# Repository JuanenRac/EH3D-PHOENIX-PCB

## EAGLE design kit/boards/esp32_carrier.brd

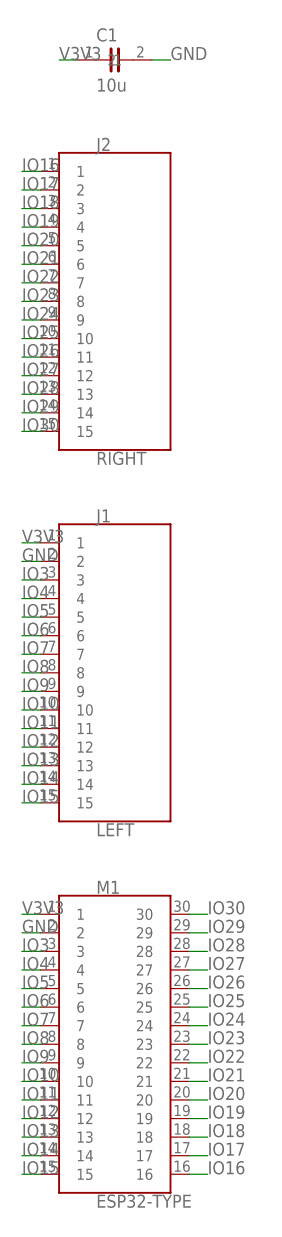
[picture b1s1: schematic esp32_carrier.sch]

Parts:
C1: 10u; CHIP-0805
J1: LEFT; HDR-1X15
J2: RIGHT; HDR-1X15
M1: ESP32-TYPE; MODULE-ESP32-TYPE

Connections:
GND: C1.2, J1.2, M1.2
IO3: J1.3, M1.3
IO4: J1.4, M1.4
IO5: J1.5, M1.5
IO6: J1.6, M1.6
IO7: J1.7, M1.7
IO8: J1.8, M1.8
IO9: J1.9, M1.9
IO10: J1.10, M1.10
IO11: J1.11, M1.11
IO12: J1.12, M1.12
IO13: J1.13, M1.13
IO14: J1.14, M1.14
IO15: J1.15, M1.15
IO16: J2.1, M1.16
IO17: J2.2, M1.17
IO18: J2.3, M1.18
IO19: J2.4, M1.19
IO20: J2.5, M1.20
IO21: J2.6, M1.21
IO22: J2.7, M1.22
IO23: J2.8, M1.23
IO24: J2.9, M1.24
IO25: J2.10, M1.25
IO26: J2.11, M1.26
IO27: J2.12, M1.27
IO28: J2.13, M1.28
IO29: J2.14, M1.29
IO30: J2.15, M1.30
V3V3: C1.1, J1.1, M1.1

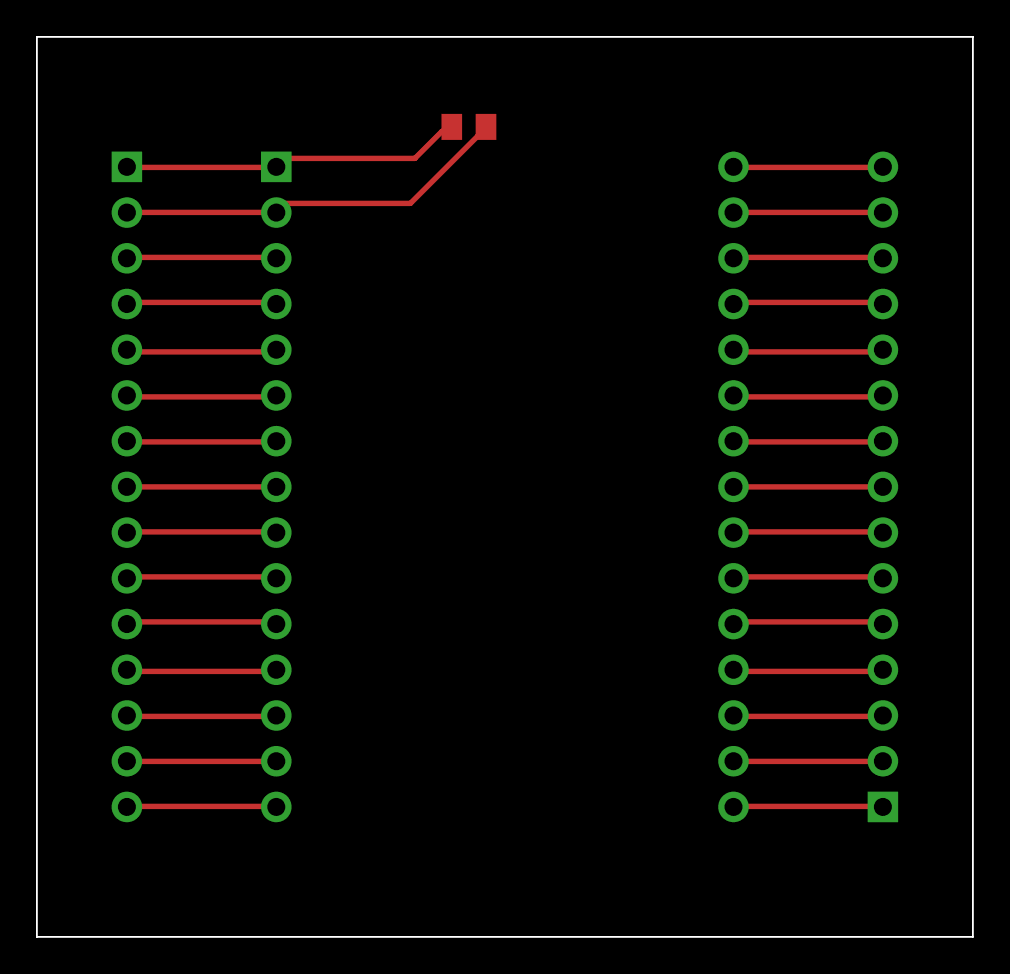
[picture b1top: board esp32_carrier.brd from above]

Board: 1 copper layer, 52.0 x 50.0 mm, 4 parts (0 on the bottom side), 30 nets.

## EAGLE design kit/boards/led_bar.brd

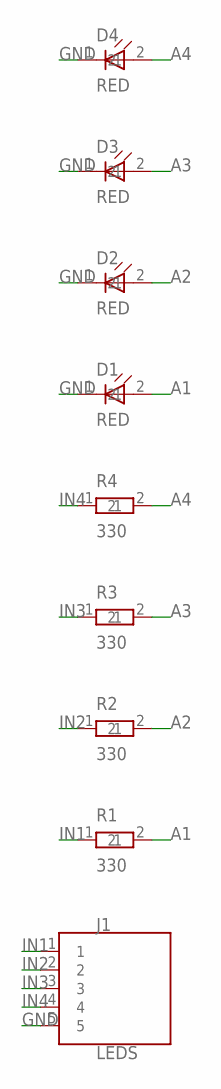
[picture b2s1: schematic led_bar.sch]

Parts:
D1, D2, D3, D4: RED; LED-0603
J1: LEDS; HDR-1X05
R1, R2, R3, R4: 330; CHIP-0603

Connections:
A1: D1.2, R1.2
A2: D2.2, R2.2
A3: D3.2, R3.2
A4: D4.2, R4.2
GND: D1.1, D2.1, D3.1, D4.1, J1.5
IN1: J1.1, R1.1
IN2: J1.2, R2.1
IN3: J1.3, R3.1
IN4: J1.4, R4.1

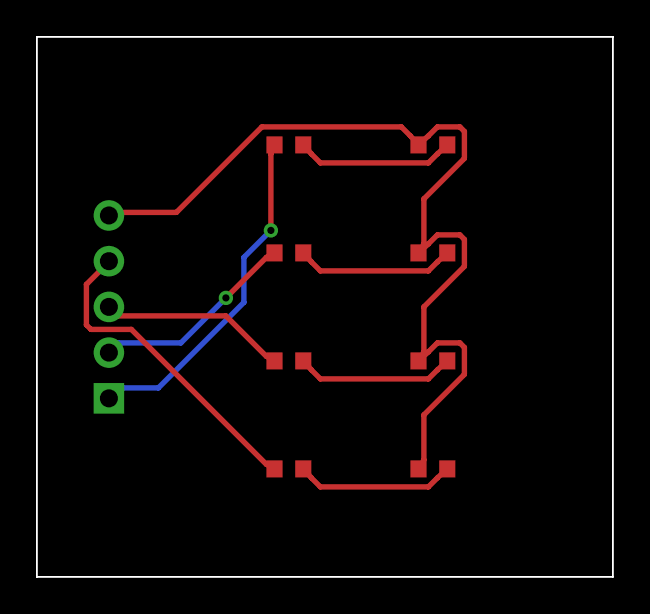
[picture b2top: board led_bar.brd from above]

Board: 2 copper layers, 32.0 x 30.0 mm, 9 parts (0 on the bottom side), 9 nets.

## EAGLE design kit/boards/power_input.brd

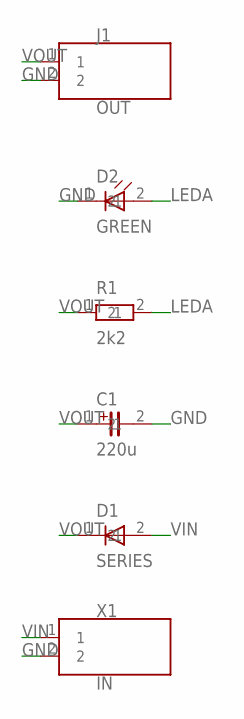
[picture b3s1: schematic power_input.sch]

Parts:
C1: 220u; C-ELEC-D8
D1: SERIES; SOD-123
D2: GREEN; LED-0805
J1: OUT; HDR-1X02
R1: 2k2; CHIP-1206
X1: IN; TERM-2P-5.0

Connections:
GND: C1.2, D2.1, J1.2, X1.2
LEDA: D2.2, R1.2
VIN: D1.2, X1.1
VOUT: C1.1, D1.1, J1.1, R1.1

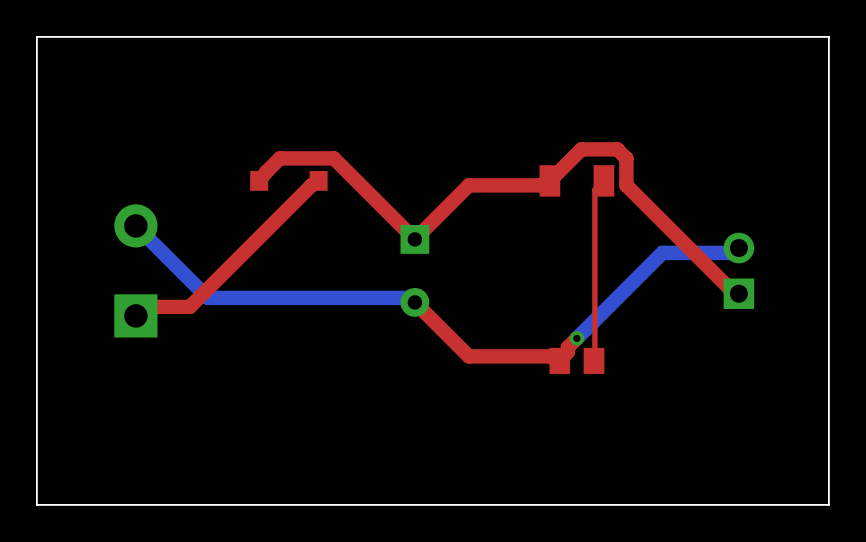
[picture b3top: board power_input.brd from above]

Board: 2 copper layers, 44.0 x 26.0 mm, 6 parts (0 on the bottom side), 4 nets.

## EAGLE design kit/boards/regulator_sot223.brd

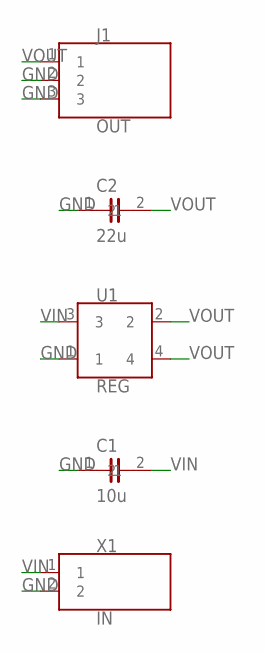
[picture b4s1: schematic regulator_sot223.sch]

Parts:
C1: 10u; CHIP-0805
C2: 22u; CHIP-0805
J1: OUT; HDR-1X03
U1: REG; SOT-223
X1: IN; TERM-2P-5.0

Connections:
GND: C1.1, C2.1, J1.2, J1.3, U1.1, X1.2
VIN: C1.2, U1.3, X1.1
VOUT: C2.2, J1.1, U1.2, U1.4

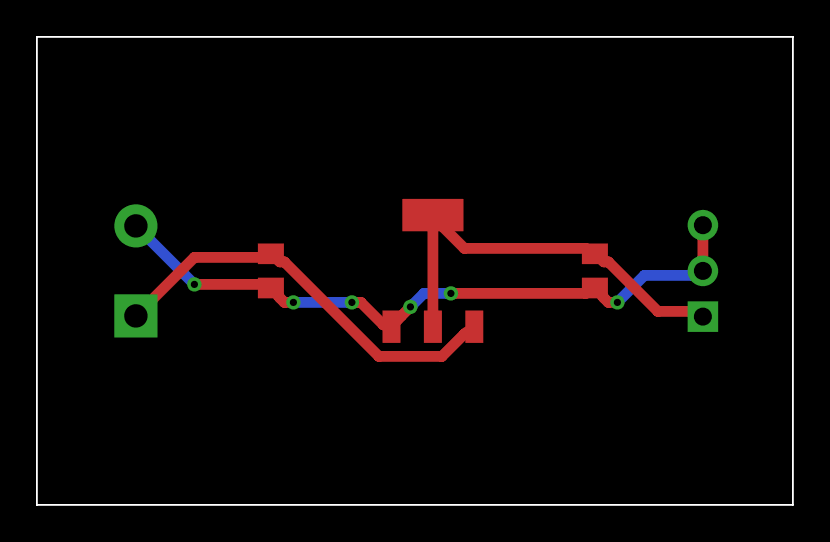
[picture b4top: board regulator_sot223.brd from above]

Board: 2 copper layers, 42.0 x 26.0 mm, 5 parts (0 on the bottom side), 3 nets.

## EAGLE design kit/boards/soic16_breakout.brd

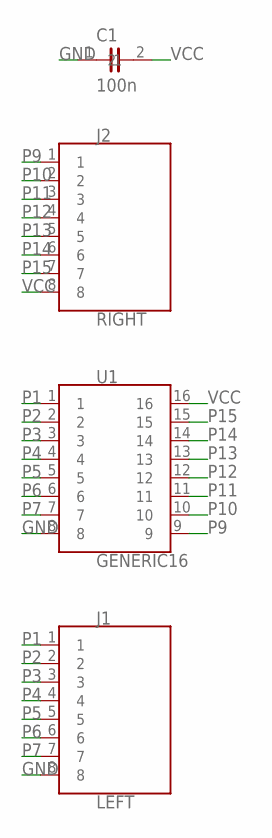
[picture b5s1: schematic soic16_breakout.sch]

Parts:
C1: 100n; CHIP-0805
J1: LEFT; HDR-1X08
J2: RIGHT; HDR-1X08
U1: GENERIC16; SOIC-16

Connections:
GND: C1.1, J1.8, U1.8
P1: J1.1, U1.1
P2: J1.2, U1.2
P3: J1.3, U1.3
P4: J1.4, U1.4
P5: J1.5, U1.5
P6: J1.6, U1.6
P7: J1.7, U1.7
P9: J2.1, U1.9
P10: J2.2, U1.10
P11: J2.3, U1.11
P12: J2.4, U1.12
P13: J2.5, U1.13
P14: J2.6, U1.14
P15: J2.7, U1.15
VCC: C1.2, J2.8, U1.16

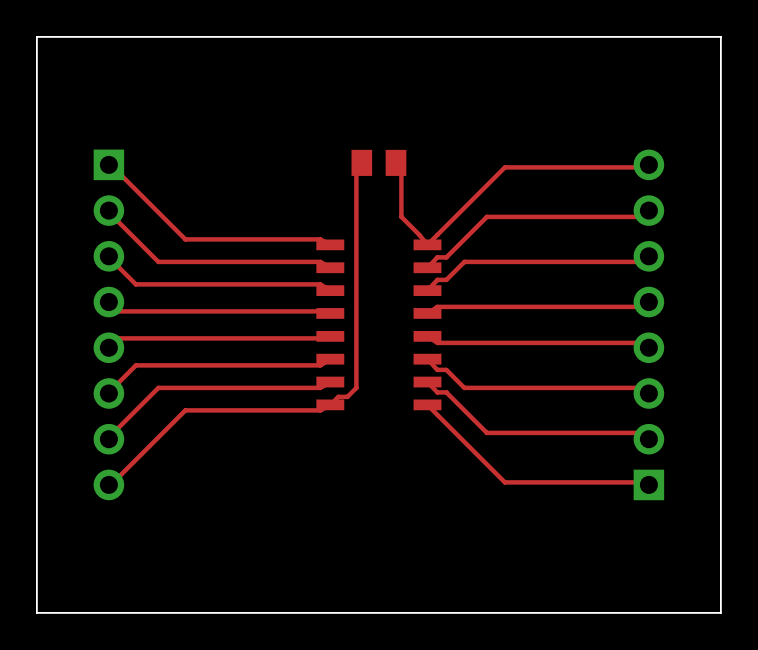
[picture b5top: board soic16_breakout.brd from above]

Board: 1 copper layer, 38.0 x 32.0 mm, 4 parts (0 on the bottom side), 16 nets.

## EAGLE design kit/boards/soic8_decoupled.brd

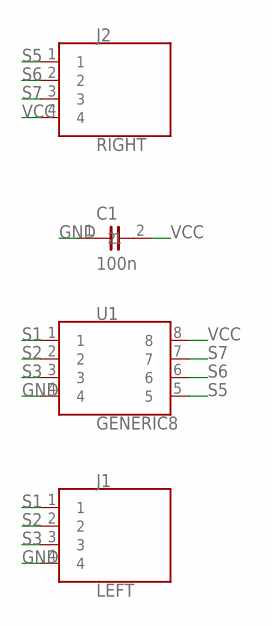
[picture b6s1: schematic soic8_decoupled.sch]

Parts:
C1: 100n; CHIP-0603
J1: LEFT; HDR-1X04
J2: RIGHT; HDR-1X04
U1: GENERIC8; SOIC-8

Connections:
GND: C1.1, J1.4, U1.4
S1: J1.1, U1.1
S2: J1.2, U1.2
S3: J1.3, U1.3
S5: J2.1, U1.5
S6: J2.2, U1.6
S7: J2.3, U1.7
VCC: C1.2, J2.4, U1.8

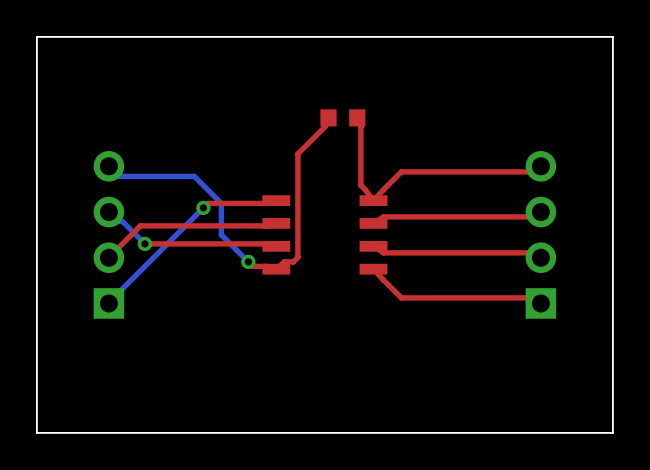
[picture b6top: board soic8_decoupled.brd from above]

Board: 2 copper layers, 32.0 x 22.0 mm, 4 parts (0 on the bottom side), 8 nets.

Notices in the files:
kit/boards/esp32_carrier.brd:
EH3D-PHOENIX-PCB starter kit. SPDX-License-Identifier: GPL-3.0-or-later. Own work, not verified.
